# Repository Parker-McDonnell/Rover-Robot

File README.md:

# Rover-Robot
Repository for Rover Robot related files i.e. ECAD, MCAD, Software and documentation

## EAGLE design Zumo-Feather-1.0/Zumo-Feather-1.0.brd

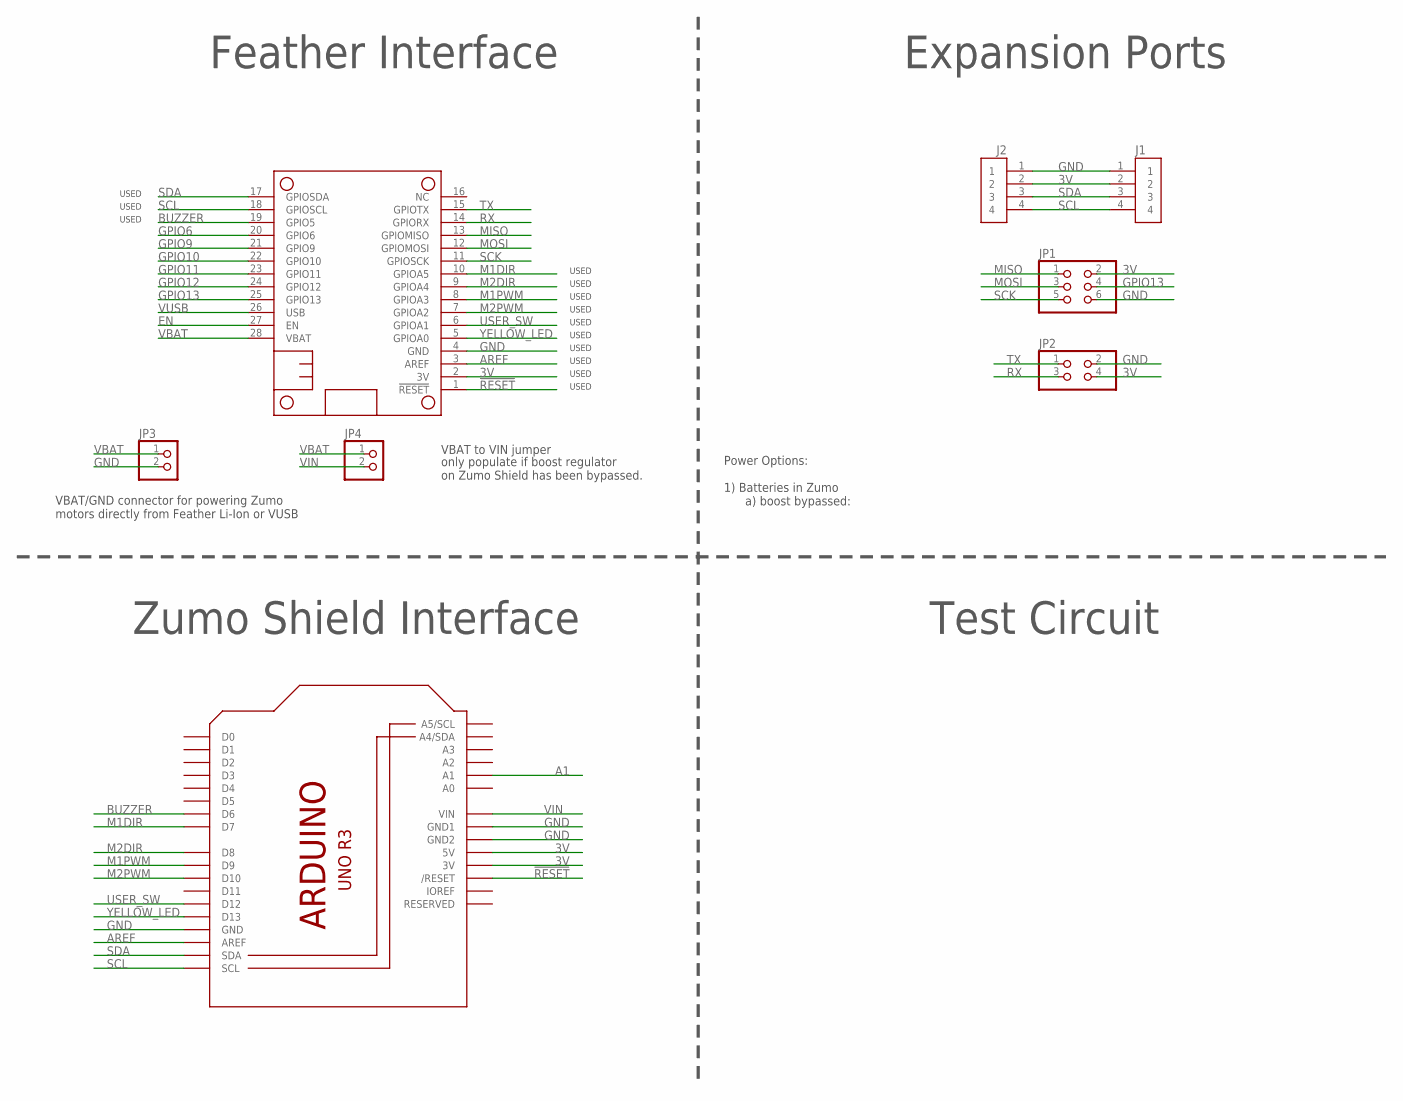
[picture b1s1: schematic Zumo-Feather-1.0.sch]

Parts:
J1, J2: CON-SM04B-SRSS-TB; JST_SH_4X1
JP1: PINHD-2X3; 2X03
JP2: PINHD-2X2; 2X02
JP3, JP4: PINHD-1X2; 1X02
MS1: BRD-FEATHERWING_NODIM_NOMNT; FEATHERWING_DIM_MNT
U1: BRD-ARDUINOR3-DIMENSION; ARDUINOR3

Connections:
3V: J1.2, J2.2, JP1.2, JP2.4, MS1.2 (3V), U1.3V, U1.5V
!RESET: MS1.1 (!RESET), U1.RESET (/RESET)
A1: U1.A1
AREF: MS1.3 (AREF), U1.AREF
BUZZER: MS1.19 (GPIO5), U1.D6
EN: MS1.27 (EN)
GND: J1.1, J2.1, JP1.6, JP2.2, JP3.2, MS1.4 (GND), U1.GND, U1.GND1, U1.GND2
GPIO6: MS1.20 (GPIO6)
GPIO9: MS1.21 (GPIO9)
GPIO10: MS1.22 (GPIO10)
GPIO11: MS1.23 (GPIO11)
GPIO12: MS1.24 (GPIO12)
GPIO13: JP1.4, MS1.25 (GPIO13)
M1DIR: MS1.10 (GPIOA5), U1.D7
M1PWM: MS1.8 (GPIOA3), U1.D9
M2DIR: MS1.9 (GPIOA4), U1.D8
M2PWM: MS1.7 (GPIOA2), U1.D10
MISO: JP1.1, MS1.13 (GPIOMISO)
MOSI: JP1.3, MS1.12 (GPIOMOSI)
RX: JP2.3, MS1.14 (GPIORX)
SCK: JP1.5, MS1.11 (GPIOSCK)
SCL: J1.4, J2.4, MS1.18 (GPIOSCL), U1.SCL
SDA: J1.3, J2.3, MS1.17 (GPIOSDA), U1.SDA
TX: JP2.1, MS1.15 (GPIOTX)
USER_SW: MS1.6 (GPIOA1), U1.D12
VBAT: JP3.1, JP4.1, MS1.28 (VBAT)
VIN: JP4.2, U1.VIN
VUSB: MS1.26 (USB)
YELLOW_LED: MS1.5 (GPIOA0), U1.D13

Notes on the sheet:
Zumo Shield Interface
Feather Interface
USED
Expansion Ports
Test Circuit
VBAT to VIN jumper
only populate if boost regulator on Zumo Shield has been bypassed.
VBAT/GND connector for powering Zumo motors directly from Feather Li-Ion or VUSB
Power Options: 1) Batteries in Zumo a) boost bypassed:

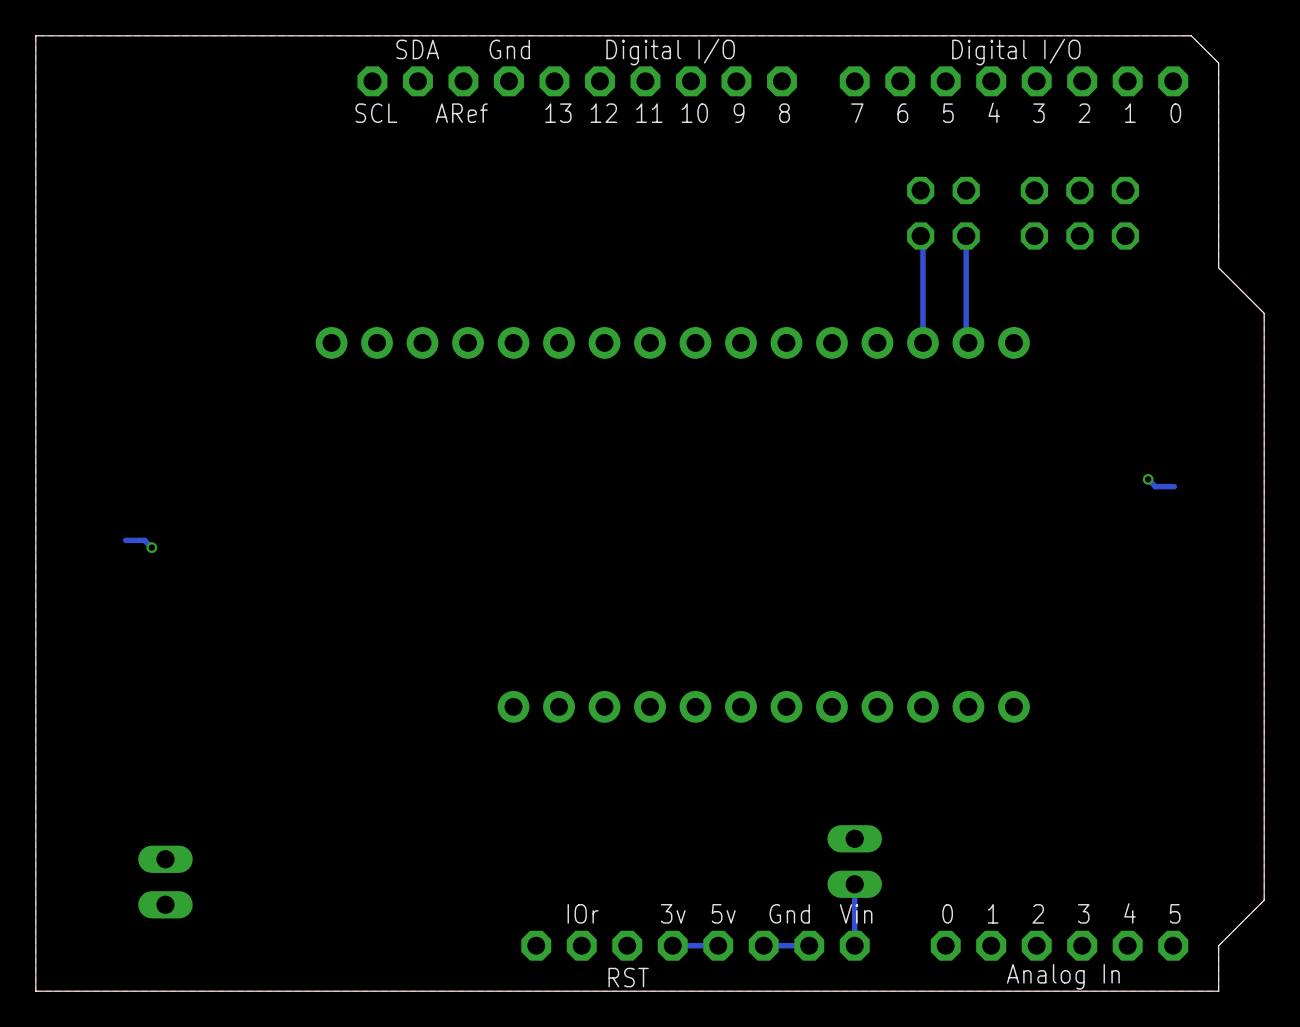
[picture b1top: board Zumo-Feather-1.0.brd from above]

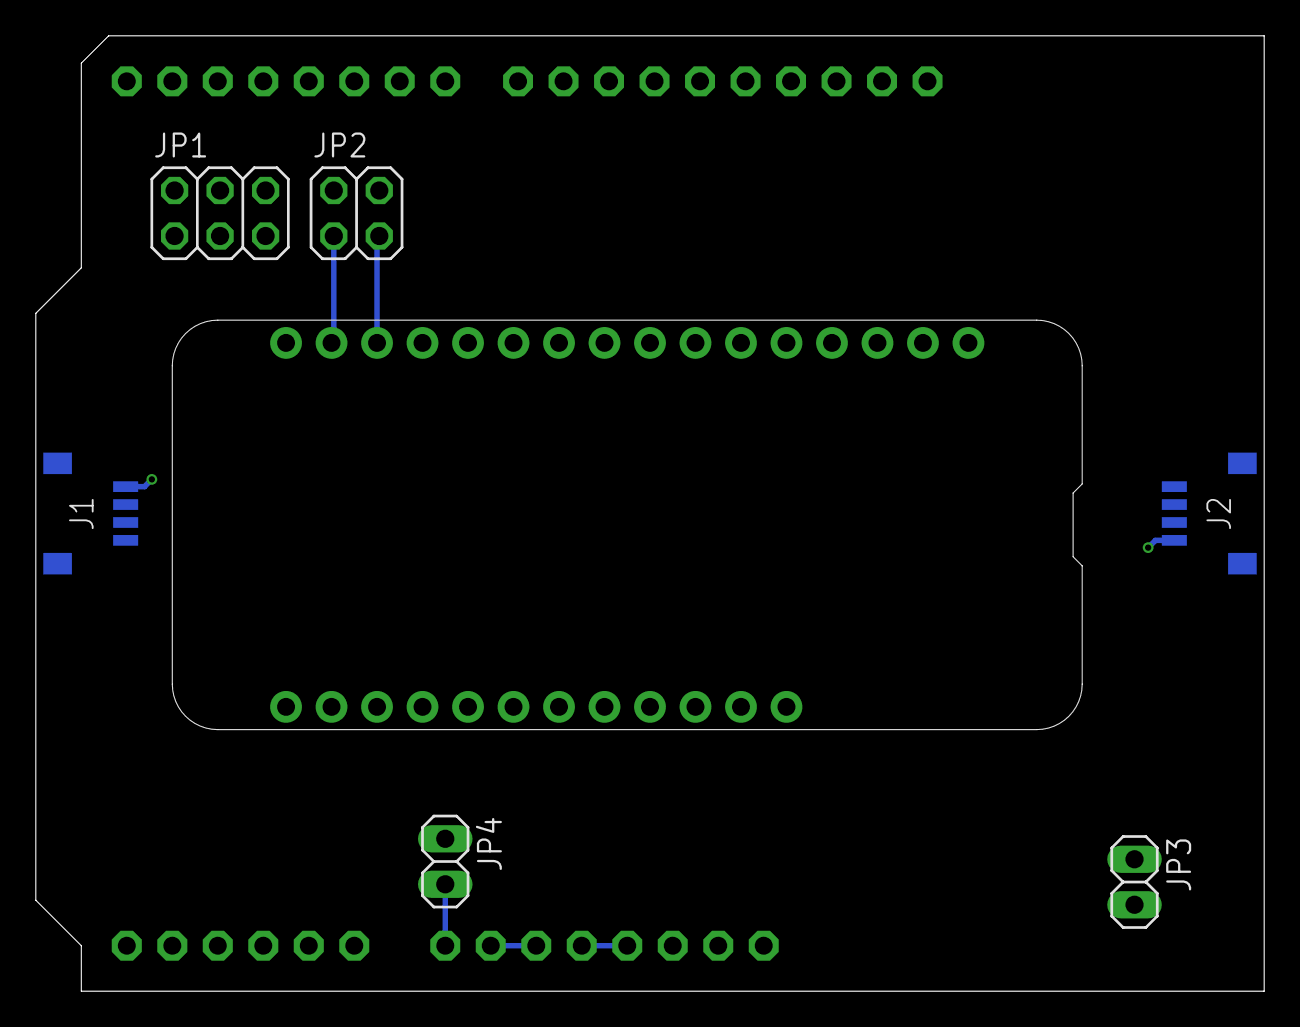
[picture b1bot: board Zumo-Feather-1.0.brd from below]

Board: 2 copper layers, 68.6 x 53.3 mm, 8 parts (7 on the bottom side), 21 nets.

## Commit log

2022-10-13 downloaded design files and started designing Feather-Zumo PCB
2022-10-14 Added CAD and worked on Feather-Zumo Interface board
2022-10-17 Worked on Zumo board
    Swapped pinout around a bunch to make layout easier. Realized power is provided by a 7.5V boost converter, which is not ideal. I will need to jumper VBATT directly from the Zumo Shield or bypass the 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
2022-10-18 Updated schematic
2022-10-20 Pushed to Fusion
